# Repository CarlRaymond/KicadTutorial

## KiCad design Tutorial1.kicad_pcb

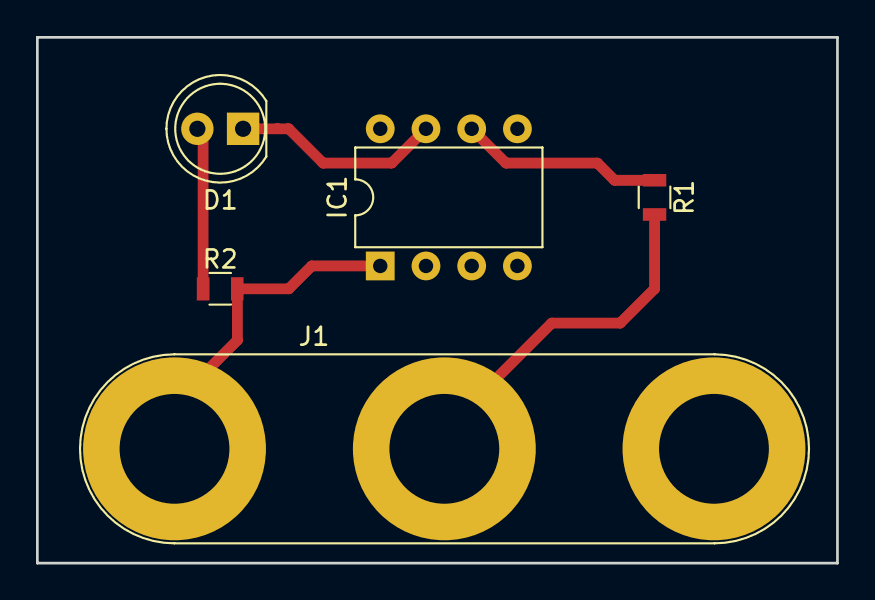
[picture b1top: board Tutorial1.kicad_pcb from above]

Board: 2 copper layers, 44.4 x 29.2 mm, 5 parts (0 on the bottom side), 6 nets.

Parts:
D1: LED; LED_D5.0mm
IC1: PIC12C508A-I/SN; DIP-8_W7.62mm
J1: MYCONN3; Banana_Jack_3Pin
R1: 100; R_0805
R2: 1K; R_0805

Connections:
/INPUT: IC1.6, R1.1
/INPUTtoR: J1.2, R1.2
/LEDtoR: D1.2, R2.1
/uCtoLED: D1.1, IC1.7
GND: IC1.8, J1.3
VCC: IC1.1, J1.1, R2.2

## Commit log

2017-03-25 Inital commit with tutorial project.
